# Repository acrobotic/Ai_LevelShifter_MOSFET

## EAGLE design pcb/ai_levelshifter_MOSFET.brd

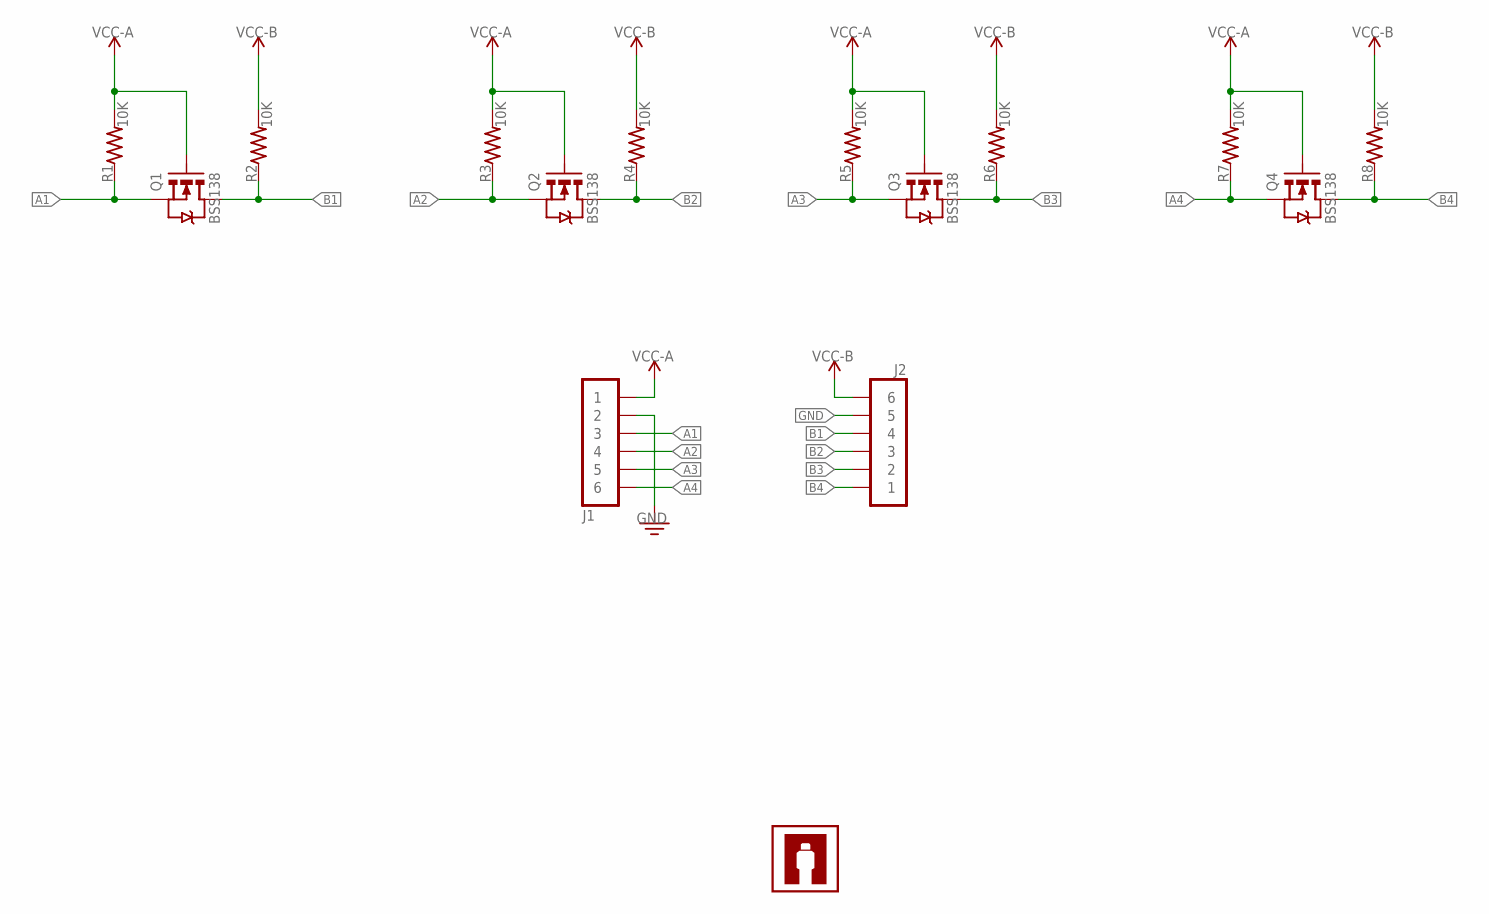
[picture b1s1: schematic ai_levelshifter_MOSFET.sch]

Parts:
J1: 1X06
J2: 1X06NOFIRST; 1X06-NOFIRST
Q1, Q2, Q3, Q4: BSS138; SOT-23
R1, R2, R3, R4, R5, R6, R7, R8: 10K; RES-0603
U$1: AI-LOGOXS; AI-LOGO-XS

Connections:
A1: J1.3, Q1.2 (S), R1.1
A2: J1.4, Q2.2 (S), R3.1
A3: J1.5, Q3.2 (S), R5.1
A4: J1.6, Q4.2 (S), R7.1
B1: J2.4, Q1.3 (D), R2.1
B2: J2.3, Q2.3 (D), R4.1
B3: J2.2, Q3.3 (D), R6.1
B4: J2.1, Q4.3 (D), R8.1
GND: J1.2, J2.5
VCC-A: J1.1, Q1.1 (G), Q2.1 (G), Q3.1 (G), Q4.1 (G), R1.2, R3.2, R5.2, R7.2
VCC-B: J2.6, R2.2, R4.2, R6.2, R8.2

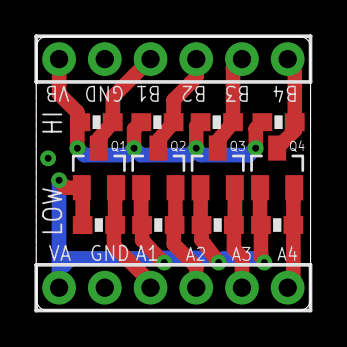
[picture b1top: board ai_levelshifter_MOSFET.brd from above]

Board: 2 copper layers, 15.2 x 15.2 mm, 15 parts (1 on the bottom side), 11 nets.

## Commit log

2014-10-21 First commit.
2014-10-21 ready for manufacturing
2015-04-24 fixed spacing to fit properly on a breadboard
2015-04-25 updating
